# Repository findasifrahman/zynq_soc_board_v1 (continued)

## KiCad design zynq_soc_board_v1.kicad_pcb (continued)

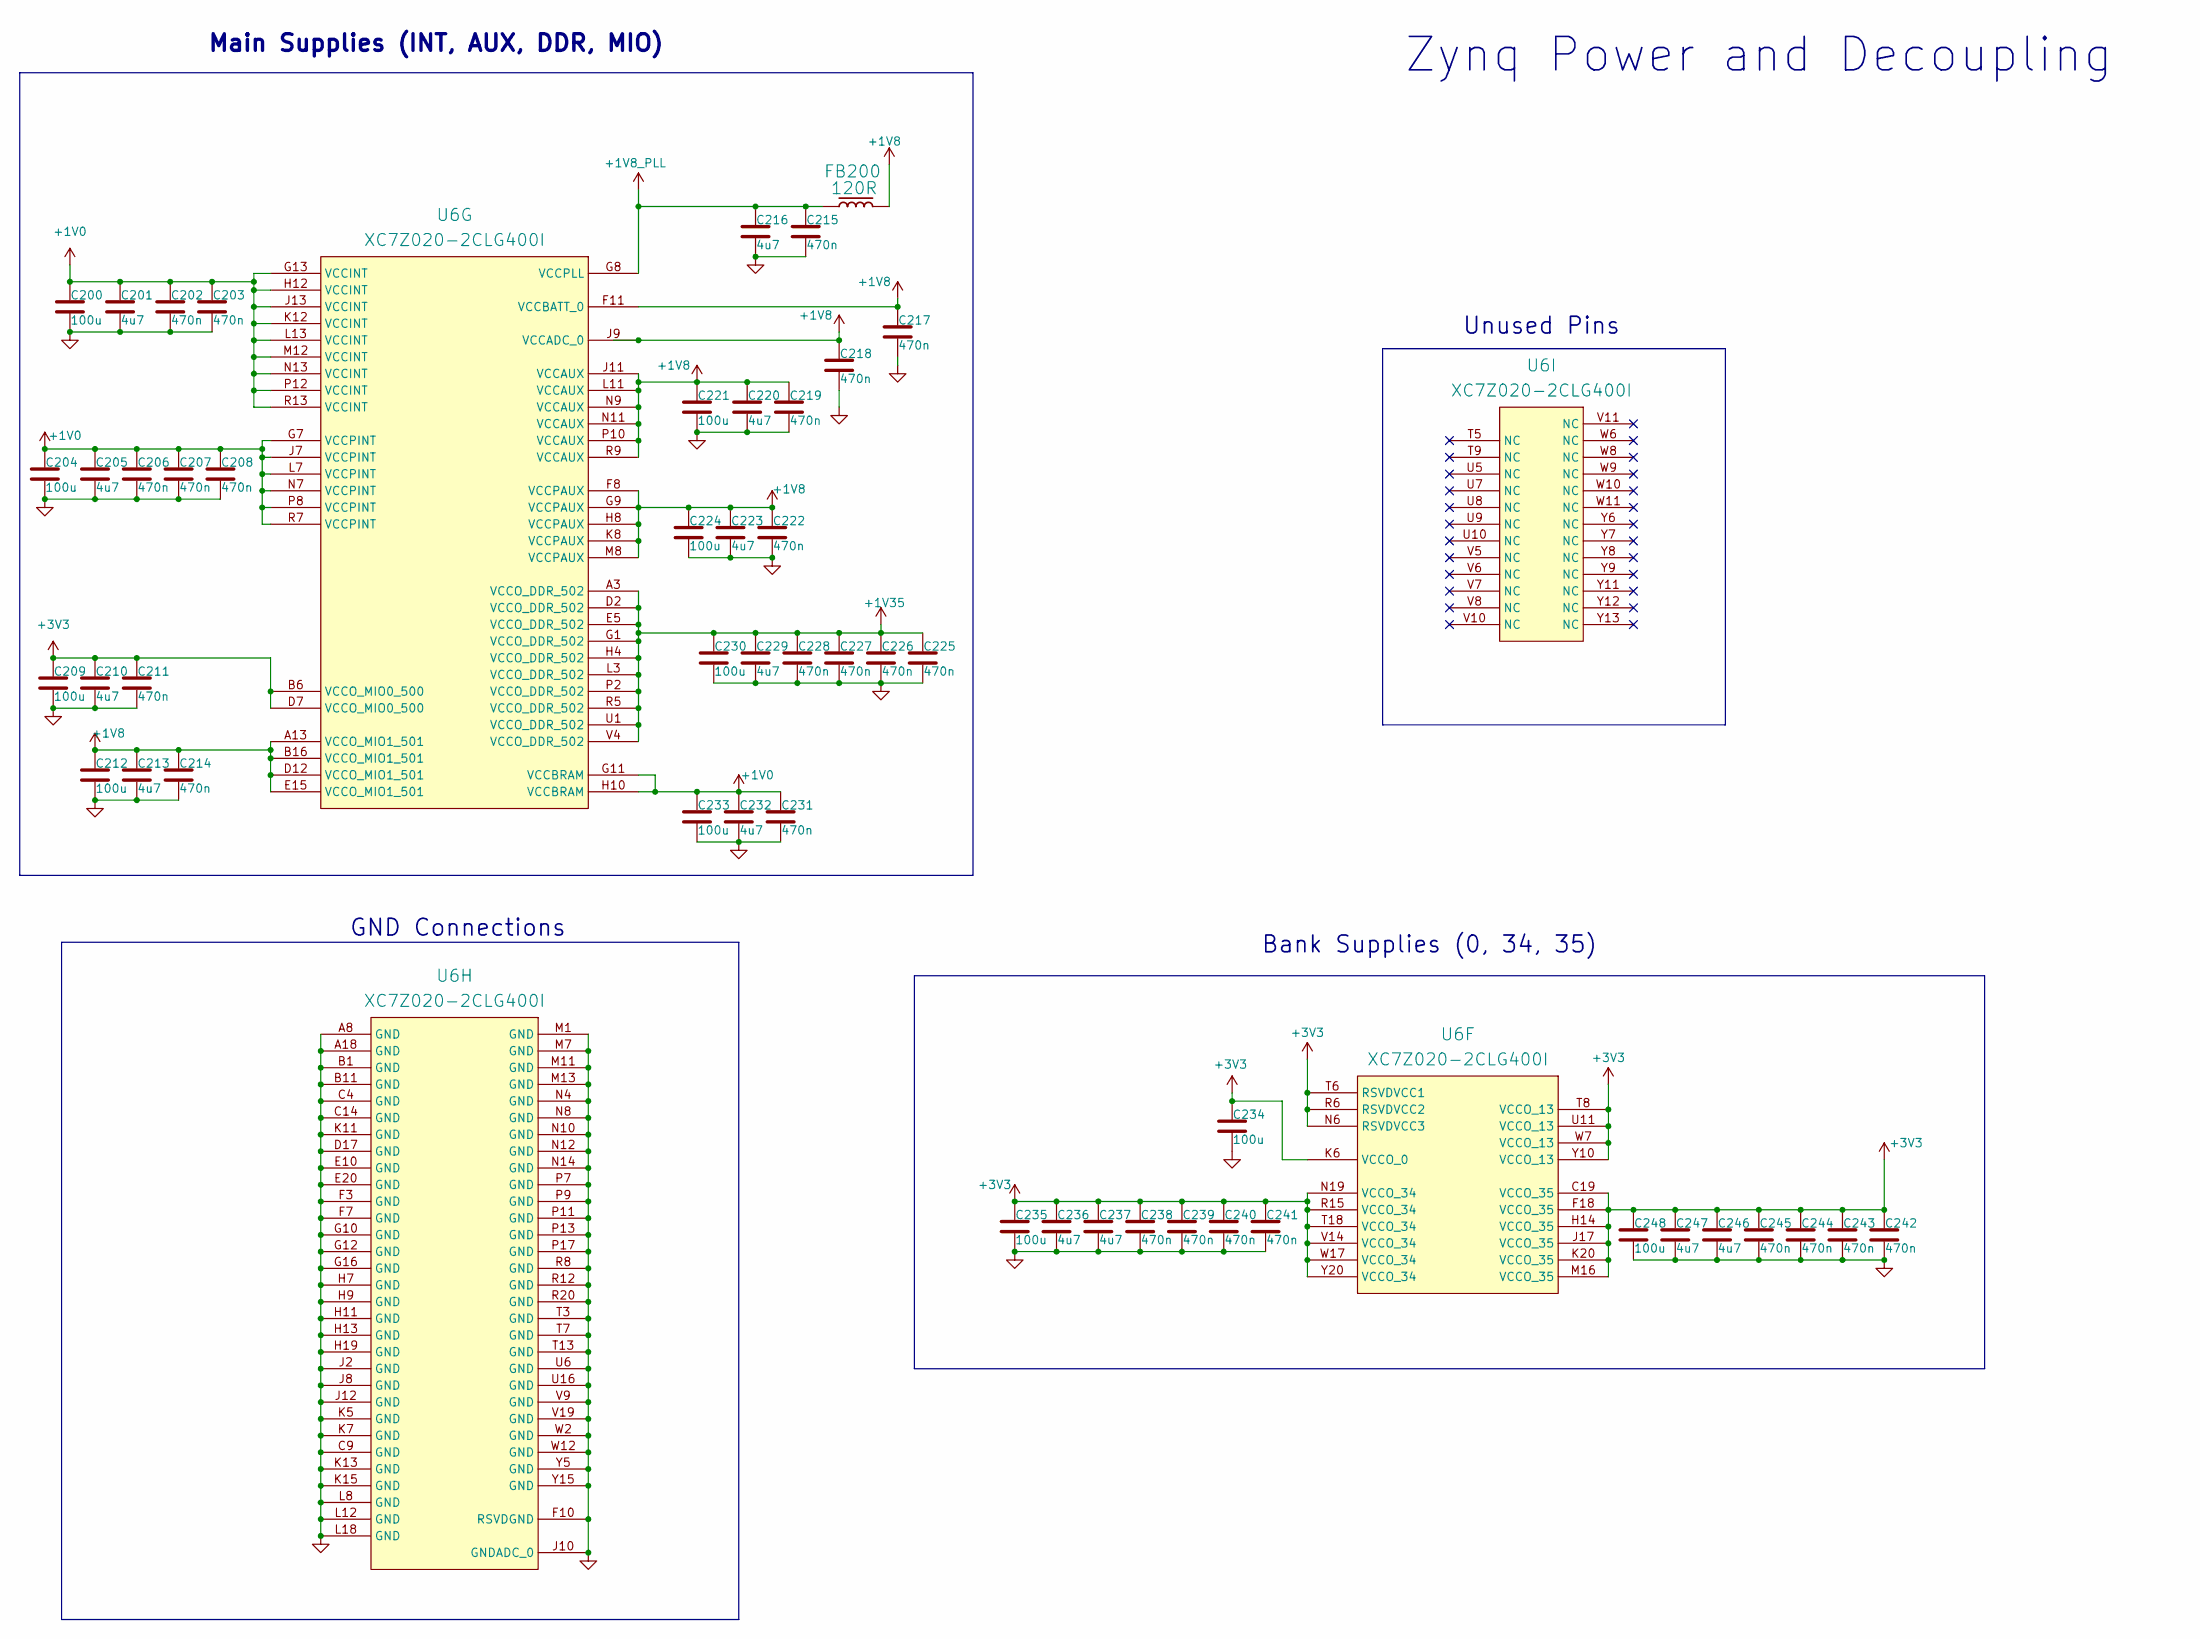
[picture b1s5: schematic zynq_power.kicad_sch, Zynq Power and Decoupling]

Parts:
C200, C204, C209, C212, C221, C224, C230, C233, C234, C235, C248: 100u; C_1206_3216Metric; Manufacturer Part Number CL31A107MQHNNNE; LCSC C15008
C201, C205, C210, C213, C216, C220, C223, C229, C232, C236, C237, C246, C247: 4u7; C_0402_1005Metric; Manufacturer Part Number CL05A475MP5NRNC; LCSC C23733
C202, C203, C206, C207, C208, C211, C214, C215, C217, C218, C219, C222, C225, C226, C227, C228, C231, C238, C239, C240, C241, C242, C243, C244, C245: 470n; C0201; Manufacturer Part Number C0603X5R1A474MT00NE; LCSC C76591
FB200: 120R; FB_0402; Manufacturer Part Number GZ1005D121TF; LCSC C38480
U6: XC7Z020-2CLG400I; Xilinx_CLG400; PartNumber XC7Z010-1CLG400C; LCSC C569043

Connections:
+1V0: C200.1, C201.1, C202.1, C203.1, C204.1, C205.1, C206.1, C207.1, C208.1, C231.1, C232.1, C233.1, U6.G7 (VCCPINT), U6.G11 (VCCBRAM), U6.G13 (VCCINT), U6.H10 (VCCBRAM), U6.H12 (VCCINT), U6.J7 (VCCPINT), U6.J13 (VCCINT), U6.K12 (VCCINT), U6.L7 (VCCPINT), U6.L13 (VCCINT), U6.M12 (VCCINT), U6.N7 (VCCPINT), U6.N13 (VCCINT), U6.P8 (VCCPINT), U6.P12 (VCCINT), U6.R7 (VCCPINT), U6.R13 (VCCINT); also elsewhere on the board
+1V8: C212.1, C213.1, C214.1, C217.1, C218.1, C219.1, C220.1, C221.1, C222.1, C223.1, C224.1, FB200.2, U6.A13 (VCCO_MIO1_501), U6.B16 (VCCO_MIO1_501), U6.D12 (VCCO_MIO1_501), U6.E15 (VCCO_MIO1_501), U6.F8 (VCCPAUX), U6.F11 (VCCBATT_0), U6.G9 (VCCPAUX), U6.H8 (VCCPAUX), U6.J9 (VCCADC_0), U6.J11 (VCCAUX), U6.K8 (VCCPAUX), U6.L11 (VCCAUX), U6.M8 (VCCPAUX), U6.N9 (VCCAUX), U6.N11 (VCCAUX), U6.P10 (VCCAUX), U6.R9 (VCCAUX); also elsewhere on the board
+1V8_PLL: C215.1, C216.1, FB200.1, U6.G8 (VCCPLL)
+1V35: C225.1, C226.1, C227.1, C228.1, C229.1, C230.1, U6.A3 (VCCO_DDR_502), U6.D2 (VCCO_DDR_502), U6.E5 (VCCO_DDR_502), U6.G1 (VCCO_DDR_502), U6.H4 (VCCO_DDR_502), U6.L3 (VCCO_DDR_502), U6.P2 (VCCO_DDR_502), U6.R5 (VCCO_DDR_502), U6.U1 (VCCO_DDR_502), U6.V4 (VCCO_DDR_502); also elsewhere on the board
+3V3: C209.1, C210.1, C211.1, C234.1, C235.1, C236.1, C237.1, C238.1, C239.1, C240.1, C241.1, C242.1, C243.1, C244.1, C245.1, C246.1, C247.1, C248.1, U6.B6 (VCCO_MIO0_500), U6.C19 (VCCO_35), U6.D7 (VCCO_MIO0_500), U6.F18 (VCCO_35), U6.H14 (VCCO_35), U6.J17 (VCCO_35), U6.K6 (VCCO_0), U6.K20 (VCCO_35), U6.M16 (VCCO_35), U6.N6 (RSVDVCC3), U6.N19 (VCCO_34), U6.R6 (RSVDVCC2), U6.R15 (VCCO_34), U6.T6 (RSVDVCC1), U6.T8 (VCCO_13), U6.T18 (VCCO_34), U6.U11 (VCCO_13), U6.V14 (VCCO_34), U6.W7 (VCCO_13), U6.W17 (VCCO_34), U6.Y10 (VCCO_13), U6.Y20 (VCCO_34); also elsewhere on the board
GND: C200.2, C201.2, C202.2, C203.2, C204.2, C205.2, C206.2, C207.2, C208.2, C209.2, C210.2, C211.2, C212.2, C213.2, C214.2, C215.2, C216.2, C217.2, C218.2, C219.2, C220.2, C221.2, C222.2, C223.2, C224.2, C225.2, C226.2, C227.2, C228.2, C229.2, C230.2, C231.2, C232.2, C233.2, C234.2, C235.2, C236.2, C237.2, C238.2, C239.2, C240.2, C241.2, C242.2, C243.2, C244.2, C245.2, C246.2, C247.2, C248.2, U6.A8 (GND), U6.A18 (GND), U6.B1 (GND), U6.B11 (GND), U6.C4 (GND), U6.C9 (GND), U6.C14 (GND), U6.D17 (GND), U6.E10 (GND), U6.E20 (GND), U6.F3 (GND), U6.F7 (GND), U6.F10 (RSVDGND), U6.G10 (GND), U6.G12 (GND), U6.G16 (GND), U6.H7 (GND), U6.H9 (GND), U6.H11 (GND), U6.H13 (GND), U6.H19 (GND), U6.J2 (GND), U6.J8 (GND), U6.J10 (GNDADC_0), U6.J12 (GND), U6.K5 (GND), U6.K7 (GND), U6.K11 (GND), U6.K13 (GND), U6.K15 (GND), U6.L8 (GND), U6.L12 (GND), U6.L18 (GND), U6.M1 (GND), U6.M7 (GND), U6.M11 (GND), U6.M13 (GND), U6.N4 (GND), U6.N8 (GND), U6.N10 (GND), U6.N12 (GND), U6.N14 (GND), U6.P7 (GND), U6.P9 (GND), U6.P11 (GND), U6.P13 (GND), U6.P17 (GND), U6.R8 (GND), U6.R12 (GND), U6.R20 (GND), U6.T3 (GND), U6.T7 (GND), U6.T13 (GND), U6.U6 (GND), U6.U16 (GND), U6.V9 (GND), U6.V19 (GND), U6.W2 (GND), U6.W12 (GND), U6.Y5 (GND), U6.Y15 (GND); also elsewhere on the board

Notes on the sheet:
Main Supplies (INT, AUX, DDR, MIO)
GND Connections
Unused Pins
Zynq Power and Decoupling
Bank Supplies (0, 34, 35)

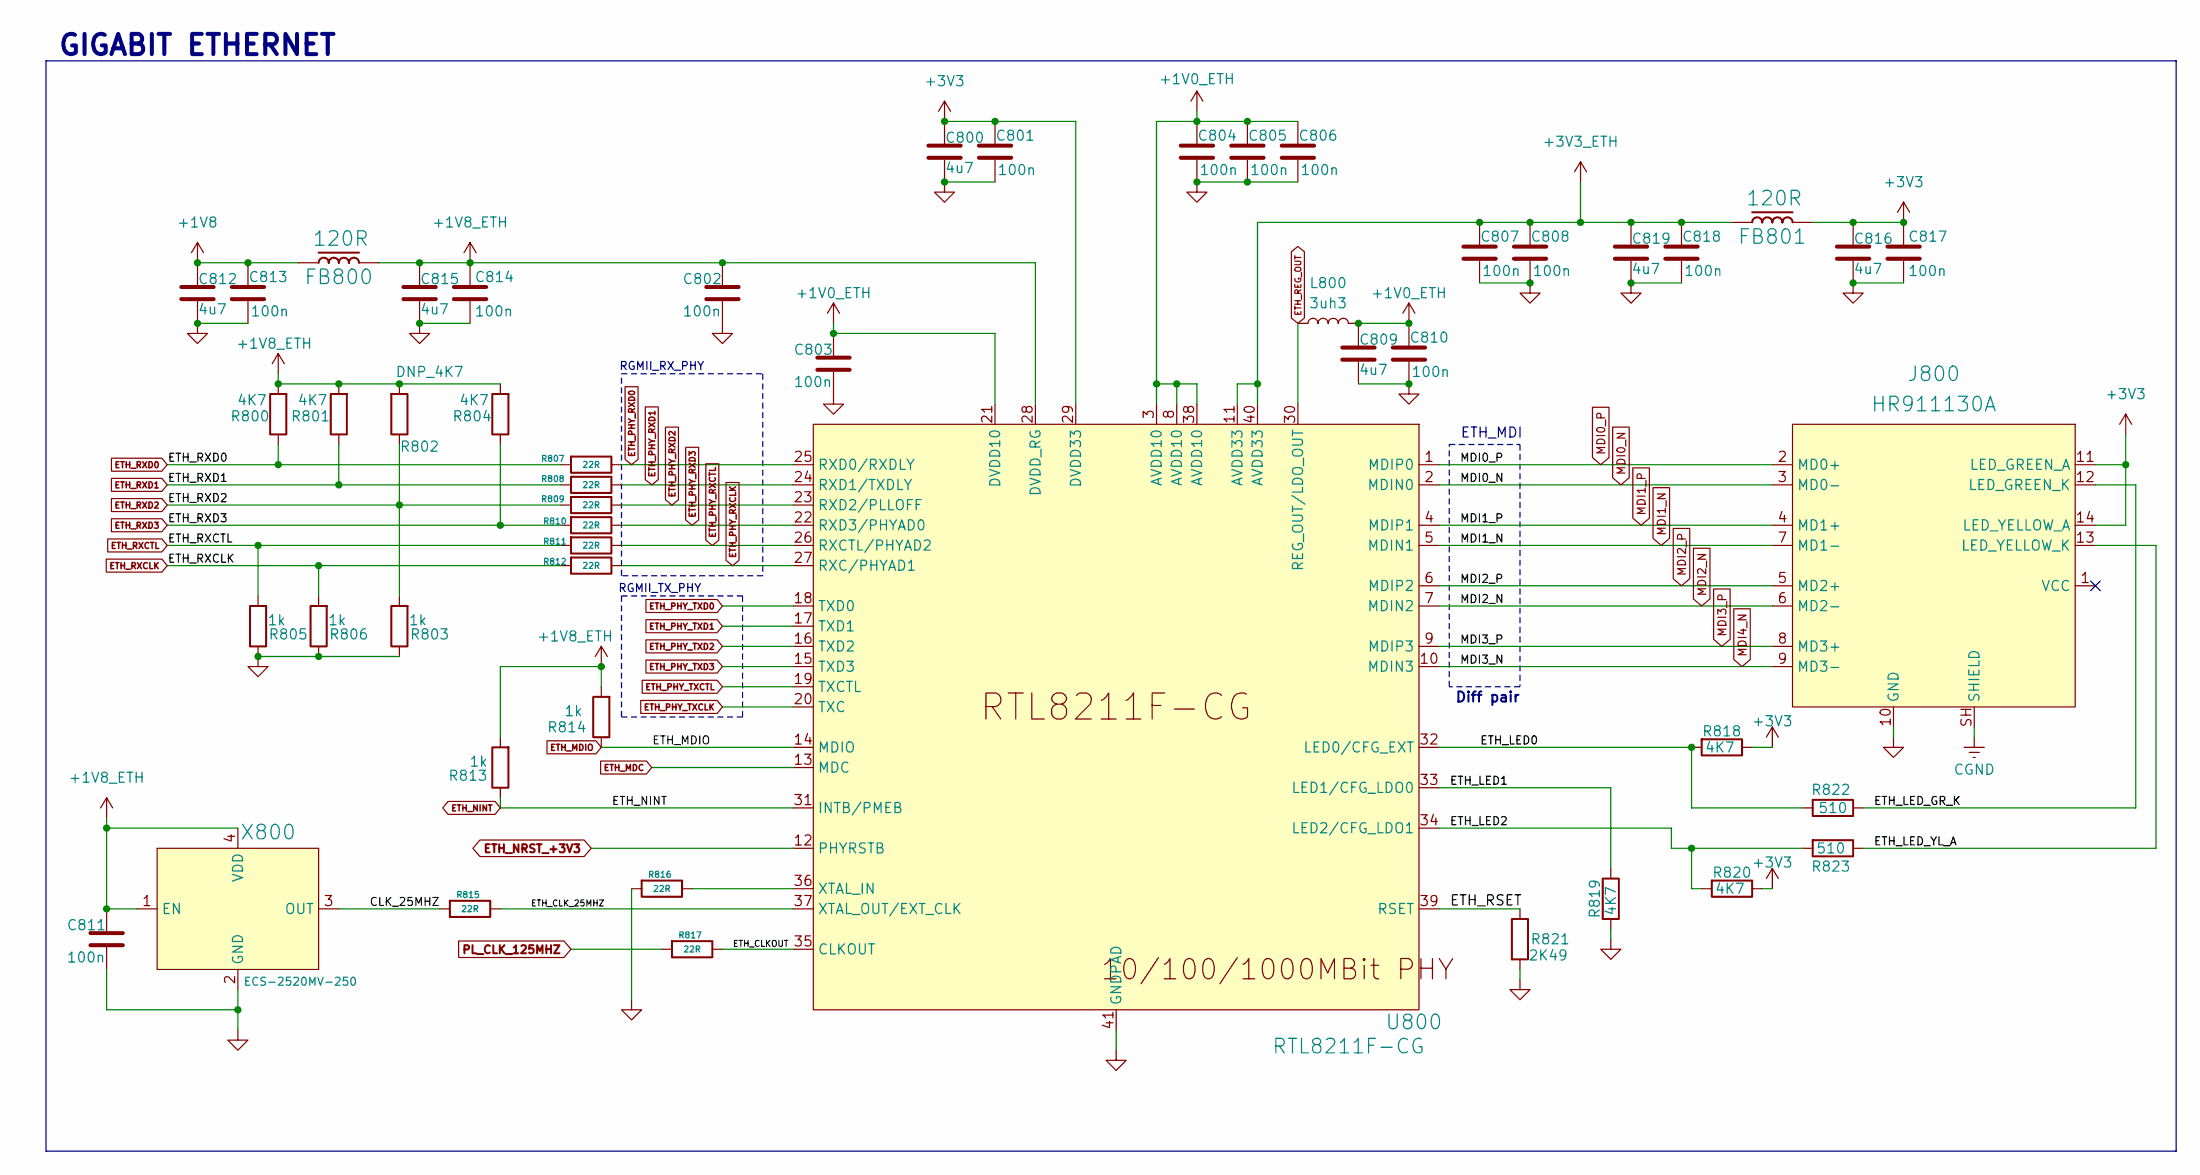
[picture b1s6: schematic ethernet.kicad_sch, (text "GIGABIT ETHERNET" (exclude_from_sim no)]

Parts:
C800, C809, C812, C815, C816, C819: 4u7; C_0402_1005Metric; Manufacturer Part Number CL05A475MP5NRNC; LCSC C23733
C801, C802, C803, C804, C805, C806, C807, C808, C810, C811, C813, C814, C817, C818: 100n; C_0402_1005Metric; Manufacturer Part Number CL05B104KO5NNNC; LCSC C1525
FB800, FB801: 120R; FB_0402; Manufacturer Part Number GZ1005D121TF; LCSC C38480
J800: HR911130A; Manufacturer Part Number HR911130A; LCSC C54408
L800: 3uh3; L_0603_1608Metric; Manufacturer Part Number LQM18PN3R3MFRL; LCSC C162581
R800, R801, R804, R818, R819, R820: 4K7; R_0402_1005Metric; Manufacturer Part Number 0402WGF4701TCE; LCSC C25900
R802: DNP_4K7; R_0402_1005Metric
R803, R805, R806, R813, R814: 1k; R_0402_1005Metric; Manufacturer Part Number 0402WGF1001TCE; LCSC C11702
R807, R808, R809, R810, R811, R812, R815, R816, R817: 22R; R_0402_1005Metric; Manufacturer Part Number 0402WGF220JTCE; LCSC C25092
R821: 2K49; R_0402_1005Metric; Manufacturer Part Number 0402WGF2491TCE; LCSC C25884
R822, R823: 510; R_0402_1005Metric; Manufacturer Part Number RC-02W511JT; LCSC C1119
U800: RTL8211F-CG; WQFN-40_L5.0-W5.0-P0.4-BL-EP; Manufacturer Part Number RTL8211F-CG; LCSC C187932
X800: ECS-2520MV-250; XTAL_2520; Manufacturer Part Number ECS-2520MV-250-BN-TR; LCSC C405463

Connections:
+1V0_ETH: C803.1, C804.1, C805.1, C806.1, C809.1, C810.1, L800.2, U800.3 (AVDD10), U800.8 (AVDD10), U800.21 (DVDD10), U800.38 (AVDD10)
+1V8: C812.1, C813.1, FB800.1; also elsewhere on the board
+1V8_ETH: C802.1, C811.1, C814.1, C815.1, FB800.2, R800.2, R801.2, R802.2, R804.2, R813.2, R814.2, U800.28 (DVDD_RG), X800.1 (EN), X800.4 (VDD)
+3V3: C800.1, C801.1, C816.1, C817.1, FB801.2, J800.11 (LED_GREEN_A), J800.14 (LED_YELLOW_A), R818.1, R820.1, U800.29 (DVDD33); also elsewhere on the board
+3V3_ETH: C807.1, C808.1, C818.1, C819.1, FB801.1, U800.11 (AVDD33), U800.40 (AVDD33)
/ethernet_gigabit/CLK_25MHZ: R815.2, X800.3 (OUT)
/ethernet_gigabit/ETH_CLKOUT: R817.1, U800.35 (CLKOUT)
/ethernet_gigabit/ETH_CLK_25MHZ: R815.1, U800.37 (XTAL_OUT/EXT_CLK)
/ethernet_gigabit/ETH_LED0: R818.2, R822.2, U800.32 (LED0/CFG_EXT)
/ethernet_gigabit/ETH_LED1: R819.1, U800.33 (LED1/CFG_LDO0)
/ethernet_gigabit/ETH_LED2: R820.2, R823.2, U800.34 (LED2/CFG_LDO1)
/ethernet_gigabit/ETH_LED_GR_K: J800.12 (LED_GREEN_K), R822.1
/ethernet_gigabit/ETH_LED_YL_A: J800.13 (LED_YELLOW_K), R823.1
/ethernet_gigabit/ETH_RSET: R821.1, U800.39 (RSET)
CGND: J800.SH (SHIELD); also elsewhere on the board
ETH_MDC: U800.13 (MDC); also elsewhere on the board
ETH_MDIO: R814.1, U800.14 (MDIO); also elsewhere on the board
ETH_NINT: R813.1, U800.31 (INTB/PMEB); also elsewhere on the board
ETH_NRST_+3V3: U800.12 (PHYRSTB); also elsewhere on the board
ETH_PHY_RXCLK: R812.1, U800.27 (RXC/PHYAD1)
ETH_PHY_RXCTL: R811.1, U800.26 (RXCTL/PHYAD2)
ETH_PHY_RXD0: R807.1, U800.25 (RXD0/RXDLY)
ETH_PHY_RXD1: R808.1, U800.24 (RXD1/TXDLY)
ETH_PHY_RXD2: R809.1, U800.23 (RXD2/PLLOFF)
ETH_PHY_RXD3: R810.1, U800.22 (RXD3/PHYAD0)
ETH_PHY_TXCLK: U800.20 (TXC); also elsewhere on the board
ETH_PHY_TXCTL: U800.19 (TXCTL); also elsewhere on the board
ETH_PHY_TXD0: U800.18 (TXD0); also elsewhere on the board
ETH_PHY_TXD1: U800.17 (TXD1); also elsewhere on the board
ETH_PHY_TXD2: U800.16 (TXD2); also elsewhere on the board
ETH_PHY_TXD3: U800.15 (TXD3); also elsewhere on the board
ETH_REG_OUT: L800.1, U800.30 (REG_OUT/LDO_OUT)
ETH_RXCLK: R806.2, R812.2; also elsewhere on the board
ETH_RXCTL: R805.2, R811.2; also elsewhere on the board
ETH_RXD0: R800.1, R807.2; also elsewhere on the board
ETH_RXD1: R801.1, R808.2; also elsewhere on the board
ETH_RXD2: R802.1, R803.2, R809.2; also elsewhere on the board
ETH_RXD3: R804.1, R810.2; also elsewhere on the board
GND: C800.2, C801.2, C802.2, C803.2, C804.2, C805.2, C806.2, C807.2, C808.2, C809.2, C810.2, C811.2, C812.2, C813.2, C814.2, C815.2, C816.2, C817.2, C818.2, C819.2, J800.10 (GND), R803.1, R805.1, R806.1, R816.2, R819.2, R821.2, U800.41 (GNDPAD), X800.2 (GND); also elsewhere on the board
MDI0_N: J800.3 (MD0-), U800.2 (MDIN0)
MDI0_P: J800.2 (MD0+), U800.1 (MDIP0)
MDI1_N: J800.7 (MD1-), U800.5 (MDIN1)
MDI1_P: J800.4 (MD1+), U800.4 (MDIP1)
MDI2_N: J800.6 (MD2-), U800.7 (MDIN2)
MDI2_P: J800.5 (MD2+), U800.6 (MDIP2)
MDI3_P: J800.8 (MD3+), U800.9 (MDIP3)
MDI4_N: J800.9 (MD3-), U800.10 (MDIN3)
unnamed: R816.1, U800.36 (XTAL_IN)
PL_CLK_125MHZ: R817.2; also elsewhere on the board

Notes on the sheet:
ETH_MDI
Diff pair
RGMII_TX_PHY
GIGABIT ETHERNET
RGMII_RX_PHY

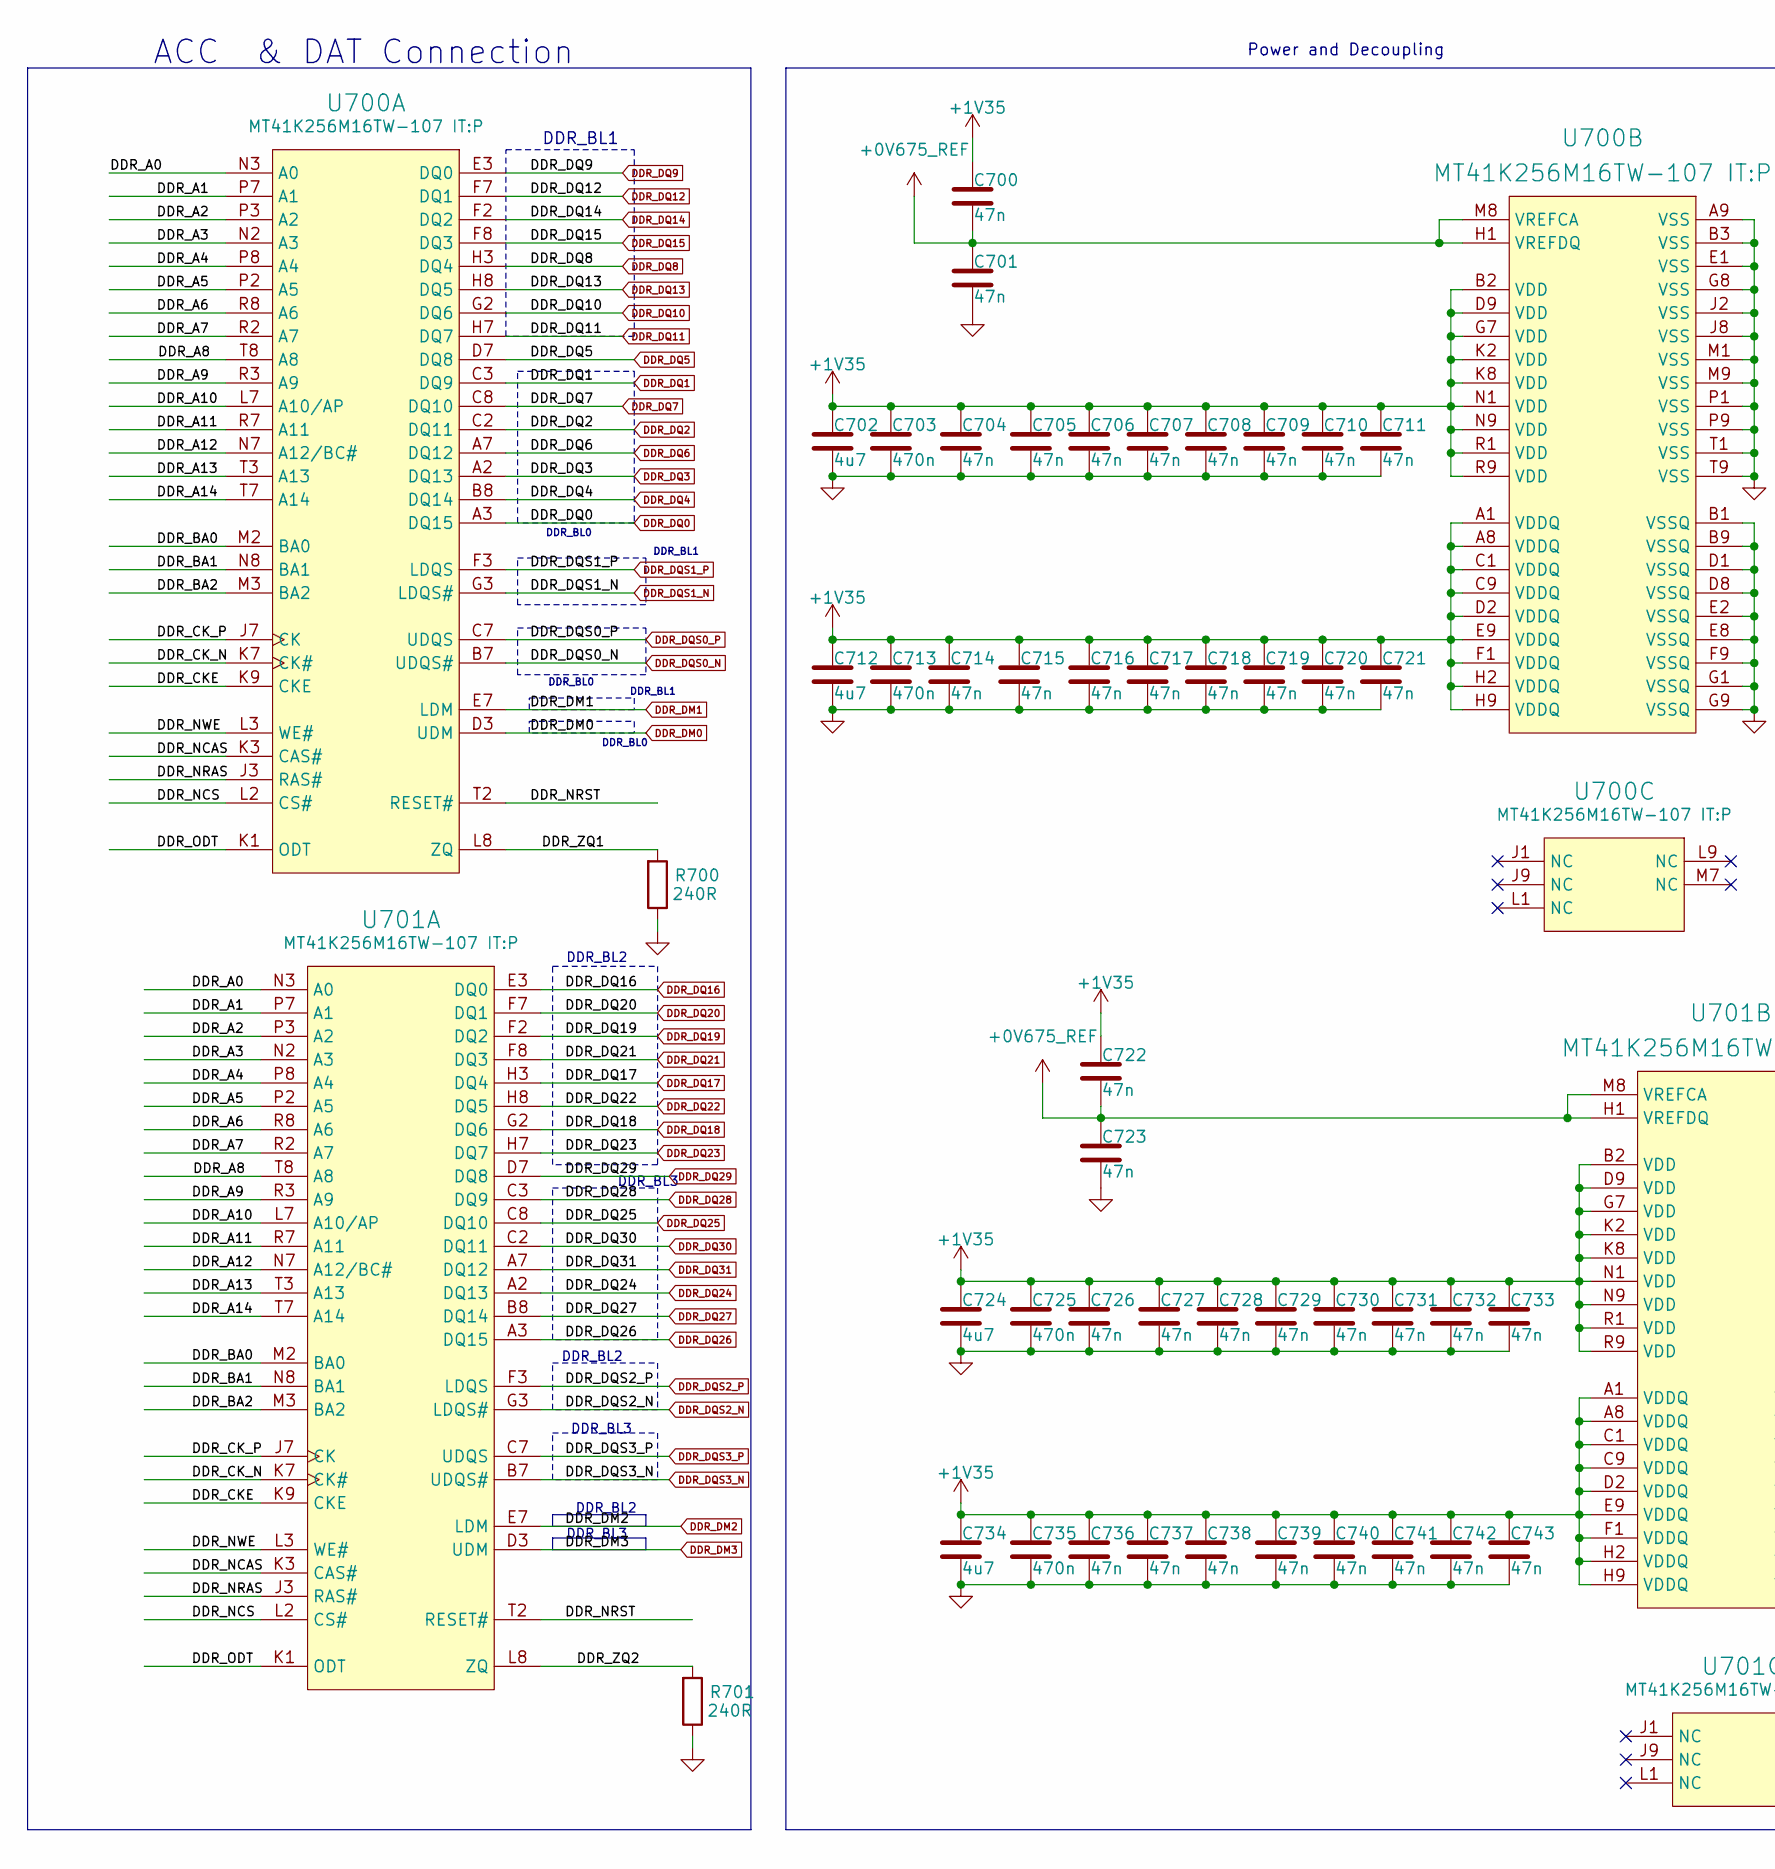
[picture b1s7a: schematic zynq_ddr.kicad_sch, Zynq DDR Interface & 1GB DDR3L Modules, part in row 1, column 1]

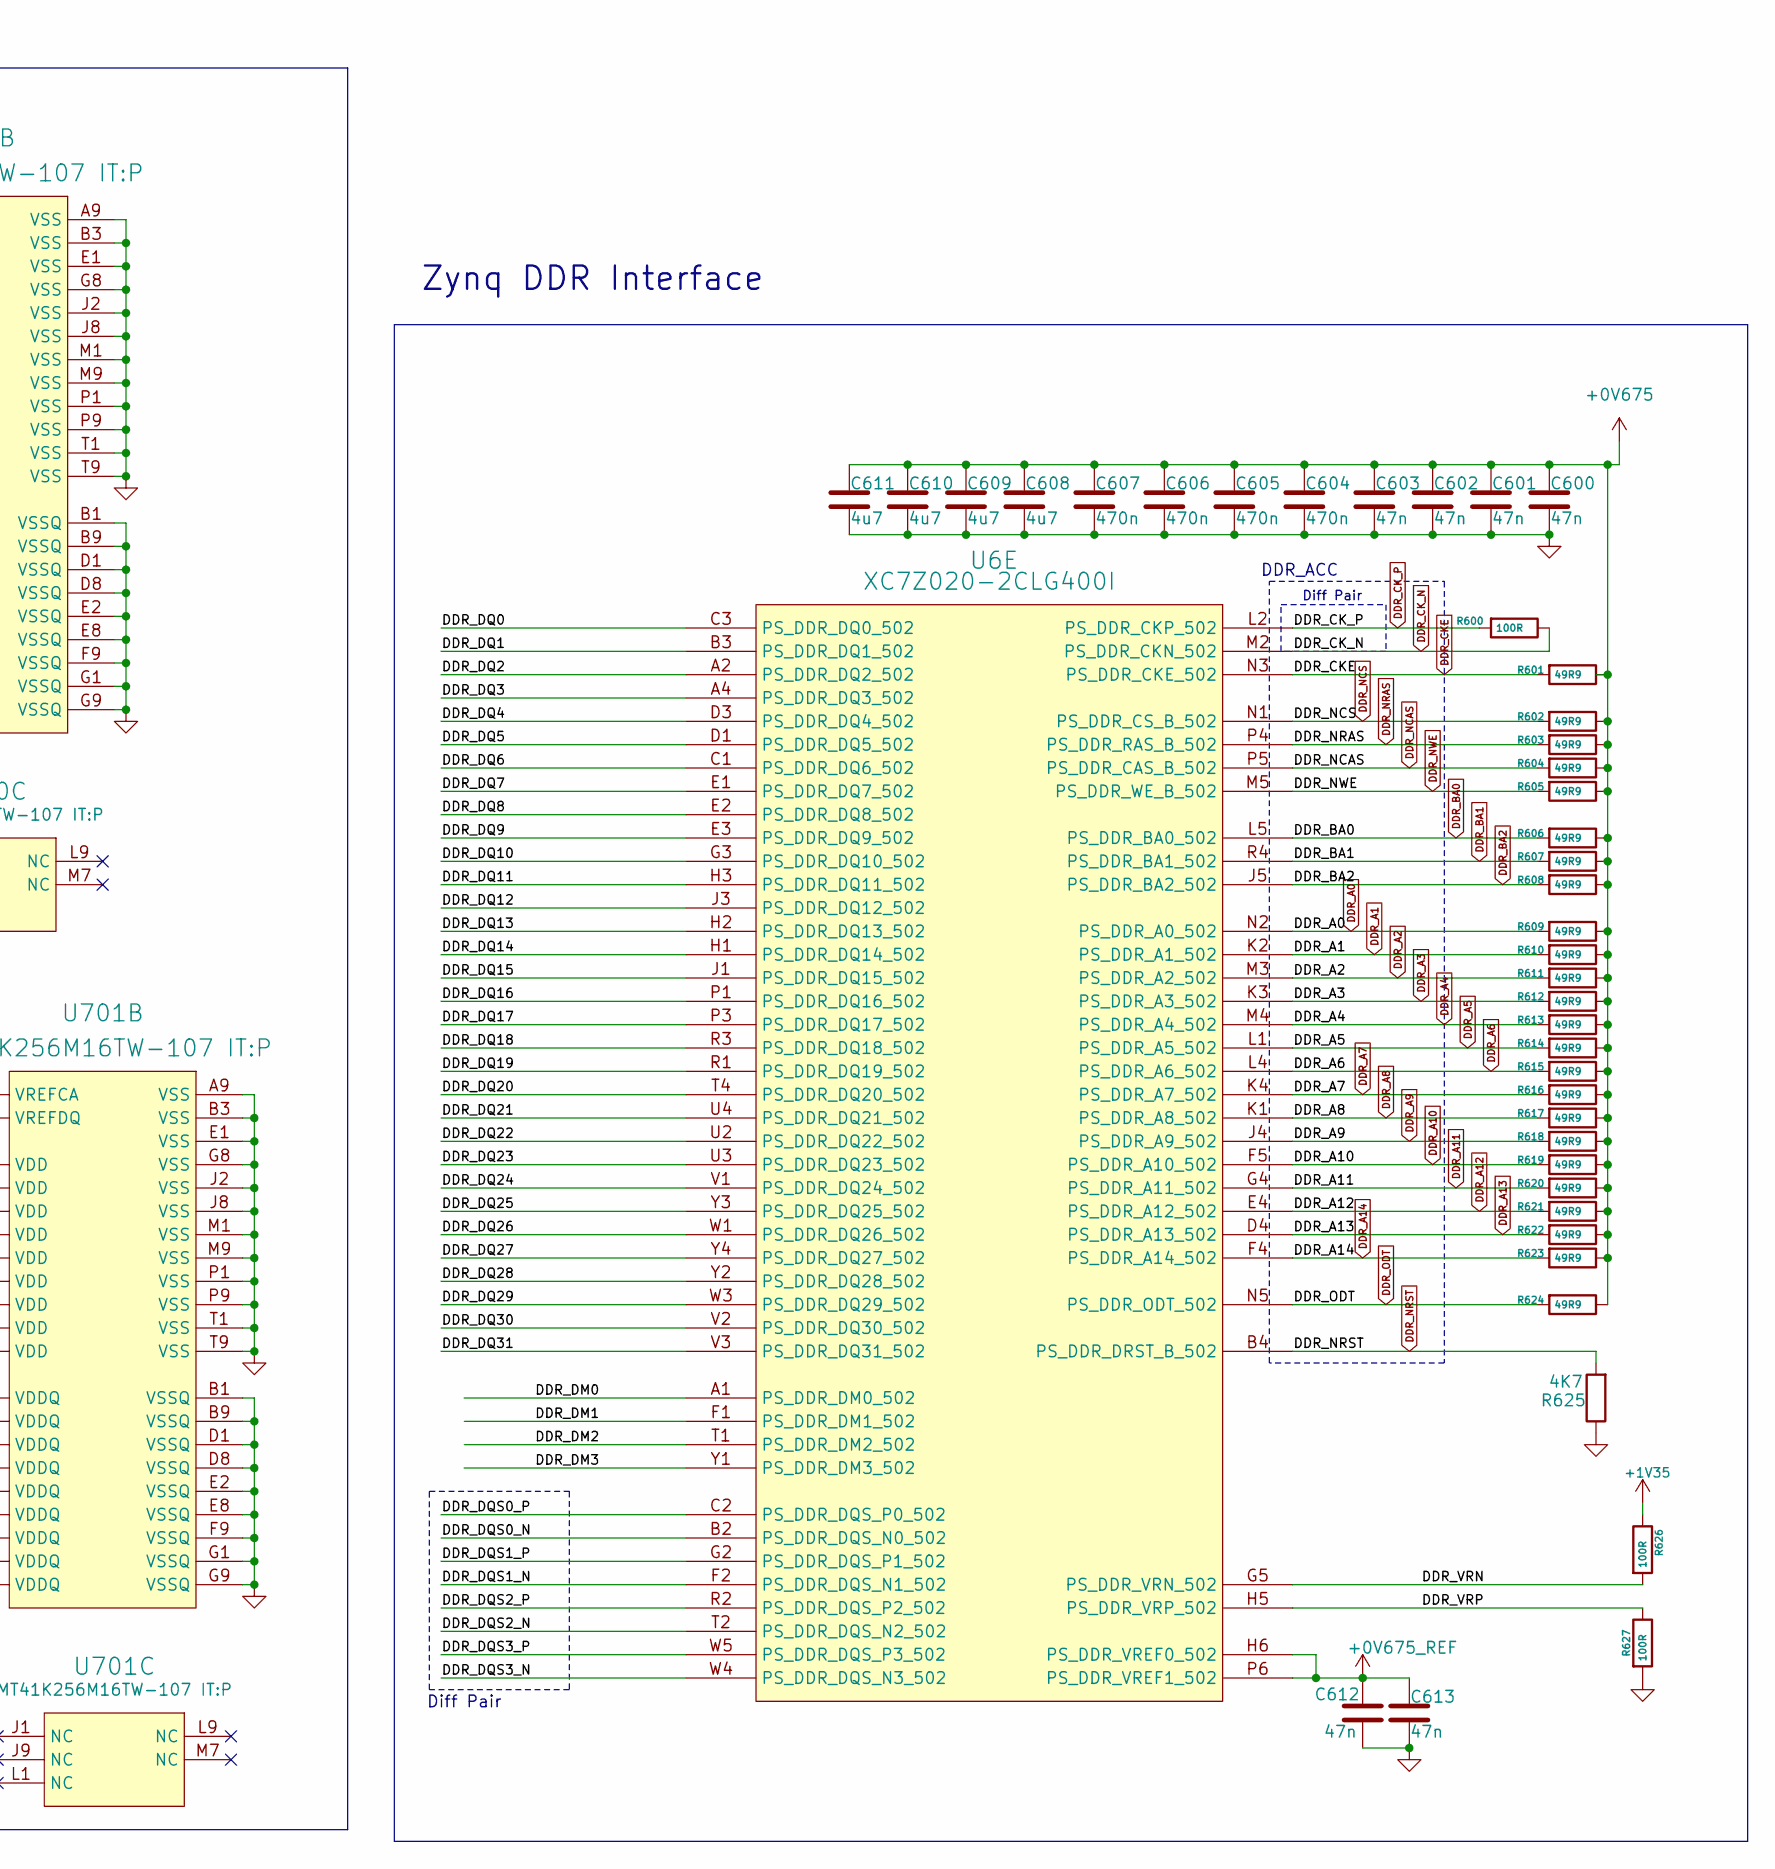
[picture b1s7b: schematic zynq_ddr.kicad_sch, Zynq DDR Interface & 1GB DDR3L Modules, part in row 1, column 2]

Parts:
C600, C601, C602, C603, C612, C613, C700, C701, C704, C705, C706, C707, C708, C709, C710, C711, C714, C715, C716, C717, C718, C719, C720, C721, C722, C723: 47n; C0201; Manufacturer Part Number GRM033R61C473KE84D; LCSC C88917
C604, C605, C606, C607, C703, C713: 470n; C0201; Manufacturer Part Number C0603X5R1A474MT00NE; LCSC C76591
C608, C609, C610, C611, C702, C724, C734: 4u7; C_0402_1005Metric; Manufacturer Part Number CL05A475MP5NRNC; LCSC C23733
C712: 4u7; C0201; Manufacturer Part Number CL05A475MP5NRNC; LCSC C23733
C725, C735: 470n; C_0201_0603Metric; Manufacturer Part Number C0603X5R1A474MT00NE; LCSC C76591
C726, C727, C728, C729, C730, C731, C732, C733, C736, C737, C738, C739, C740, C741, C742, C743: 47n; C_0201_0603Metric; Manufacturer Part Number GRM033R61C473KE84D; LCSC C88917
R600, R626, R627: 100R; R0201; Manufacturer Part Number RC0201FR-07100RL; LCSC C77623
R601, R602, R603, R604, R605, R606, R607, R608, R609, R610, R611, R612, R613, R614, R615, R616, R617, R618, R619, R620, R621, R622, R623, R624: 49R9; R0201; Manufacturer Part Number RC0201FR-0749R9L; LCSC C155744
R625: 4K7; R_0402_1005Metric; Manufacturer Part Number 0402WGF4701TCE; LCSC C25900
R700, R701: 240R; R_0402_1005Metric; Manufacturer Part Number 0402WGF2400TCE; LCSC C25094
U6: XC7Z020-2CLG400I; Xilinx_CLG400; PartNumber XC7Z010-1CLG400C; LCSC C569043
U700, U701: MT41K256M16TW-107 IT:P; FBGA-96_L14.0-W8.0-R16-C6-P0.80-TL; Manufacturer Part Number MT41K256M16TW-107 IT:P; LCSC C367428

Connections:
+0V675: C600.1, C601.1, C602.1, C603.1, C604.1, C605.1, C606.1, C607.1, C608.1, C609.1, C610.1, C611.1, R601.1, R602.1, R603.1, R604.1, R605.1, R606.1, R607.1, R608.1, R609.1, R610.1, R611.1, R612.1, R613.1, R614.1, R615.1, R616.1, R617.1, R618.1, R619.1, R620.1, R621.1, R622.1, R623.1, R624.1; also elsewhere on the board
+0V675_REF: C612.1, C613.1, C700.2, C701.1, C722.2, C723.1, U6.H6 (PS_DDR_VREF0_502), U6.P6 (PS_DDR_VREF1_502), U700.H1 (VREFDQ), U700.M8 (VREFCA), U701.H1 (VREFDQ), U701.M8 (VREFCA); also elsewhere on the board
+1V35: C700.1, C702.1, C703.1, C704.1, C705.1, C706.1, C707.1, C708.1, C709.1, C710.1, C711.1, C712.1, C713.1, C714.1, C715.1, C716.1, C717.1, C718.1, C719.1, C720.1, C721.1, C722.1, C724.1, C725.1, C726.1, C727.1, C728.1, C729.1, C730.1, C731.1, C732.1, C733.1, C734.1, C735.1, C736.1, C737.1, C738.1, C739.1, C740.1, C741.1, C742.1, C743.1, R626.1, U700.A1 (VDDQ), U700.A8 (VDDQ), U700.B2 (VDD), U700.C1 (VDDQ), U700.C9 (VDDQ), U700.D2 (VDDQ), U700.D9 (VDD), U700.E9 (VDDQ), U700.F1 (VDDQ), U700.G7 (VDD), U700.H2 (VDDQ), U700.H9 (VDDQ), U700.K2 (VDD), U700.K8 (VDD), U700.N1 (VDD), U700.N9 (VDD), U700.R1 (VDD), U700.R9 (VDD), U701.A1 (VDDQ), U701.A8 (VDDQ), U701.B2 (VDD), U701.C1 (VDDQ), U701.C9 (VDDQ), U701.D2 (VDDQ), U701.D9 (VDD), U701.E9 (VDDQ), U701.F1 (VDDQ), U701.G7 (VDD), U701.H2 (VDDQ), U701.H9 (VDDQ), U701.K2 (VDD), U701.K8 (VDD), U701.N1 (VDD), U701.N9 (VDD), U701.R1 (VDD), U701.R9 (VDD); also elsewhere on the board
/zynq_ddr/DDR_VRN: R626.2, U6.G5 (PS_DDR_VRN_502)
/zynq_ddr/DDR_VRP: R627.1, U6.H5 (PS_DDR_VRP_502)
/zynq_ddr/DDR_ZQ1: R700.2, U700.L8 (ZQ)
/zynq_ddr/DDR_ZQ2: R701.2, U701.L8 (ZQ)
DDR_A0: R609.2, U6.N2 (PS_DDR_A0_502), U700.N3 (A0), U701.N3 (A0)
DDR_A1: R610.2, U6.K2 (PS_DDR_A1_502), U700.P7 (A1), U701.P7 (A1)
DDR_A2: R611.2, U6.M3 (PS_DDR_A2_502), U700.P3 (A2), U701.P3 (A2)
DDR_A3: R612.2, U6.K3 (PS_DDR_A3_502), U700.N2 (A3), U701.N2 (A3)
DDR_A4: R613.2, U6.M4 (PS_DDR_A4_502), U700.P8 (A4), U701.P8 (A4)
DDR_A5: R614.2, U6.L1 (PS_DDR_A5_502), U700.P2 (A5), U701.P2 (A5)
DDR_A6: R615.2, U6.L4 (PS_DDR_A6_502), U700.R8 (A6), U701.R8 (A6)
DDR_A7: R616.2, U6.K4 (PS_DDR_A7_502), U700.R2 (A7), U701.R2 (A7)
DDR_A8: R617.2, U6.K1 (PS_DDR_A8_502), U700.T8 (A8), U701.T8 (A8)
DDR_A9: R618.2, U6.J4 (PS_DDR_A9_502), U700.R3 (A9), U701.R3 (A9)
DDR_A10: R619.2, U6.F5 (PS_DDR_A10_502), U700.L7 (A10/AP), U701.L7 (A10/AP)
DDR_A11: R620.2, U6.G4 (PS_DDR_A11_502), U700.R7 (A11), U701.R7 (A11)
DDR_A12: R621.2, U6.E4 (PS_DDR_A12_502), U700.N7 (A12/BC#), U701.N7 (A12/BC#)
DDR_A13: R622.2, U6.D4 (PS_DDR_A13_502), U700.T3 (A13), U701.T3 (A13)
DDR_A14: R623.2, U6.F4 (PS_DDR_A14_502), U700.T7 (A14), U701.T7 (A14)
DDR_BA0: R606.2, U6.L5 (PS_DDR_BA0_502), U700.M2 (BA0), U701.M2 (BA0)
DDR_BA1: R607.2, U6.R4 (PS_DDR_BA1_502), U700.N8 (BA1), U701.N8 (BA1)
DDR_BA2: R608.2, U6.J5 (PS_DDR_BA2_502), U700.M3 (BA2), U701.M3 (BA2)
DDR_CKE: R601.2, U6.N3 (PS_DDR_CKE_502), U700.K9 (CKE), U701.K9 (CKE)
DDR_CK_N: R600.1, U6.M2 (PS_DDR_CKN_502), U700.K7 (CK#), U701.K7 (CK#)
DDR_CK_P: R600.2, U6.L2 (PS_DDR_CKP_502), U700.J7 (CK), U701.J7 (CK)
DDR_DM0: U6.A1 (PS_DDR_DM0_502), U700.D3 (UDM)
DDR_DM1: U6.F1 (PS_DDR_DM1_502), U700.E7 (LDM)
DDR_DM2: U6.T1 (PS_DDR_DM2_502), U701.E7 (LDM)
DDR_DM3: U6.Y1 (PS_DDR_DM3_502), U701.D3 (UDM)
DDR_DQ0: U6.C3 (PS_DDR_DQ0_502), U700.A3 (DQ15)
DDR_DQ1: U6.B3 (PS_DDR_DQ1_502), U700.C3 (DQ9)
DDR_DQ2: U6.A2 (PS_DDR_DQ2_502), U700.C2 (DQ11)
DDR_DQ3: U6.A4 (PS_DDR_DQ3_502), U700.A2 (DQ13)
DDR_DQ4: U6.D3 (PS_DDR_DQ4_502), U700.B8 (DQ14)
DDR_DQ5: U6.D1 (PS_DDR_DQ5_502), U700.D7 (DQ8)
DDR_DQ6: U6.C1 (PS_DDR_DQ6_502), U700.A7 (DQ12)
DDR_DQ7: U6.E1 (PS_DDR_DQ7_502), U700.C8 (DQ10)
DDR_DQ8: U6.E2 (PS_DDR_DQ8_502), U700.H3 (DQ4)
DDR_DQ9: U6.E3 (PS_DDR_DQ9_502), U700.E3 (DQ0)
DDR_DQ10: U6.G3 (PS_DDR_DQ10_502), U700.G2 (DQ6)
DDR_DQ11: U6.H3 (PS_DDR_DQ11_502), U700.H7 (DQ7)
DDR_DQ12: U6.J3 (PS_DDR_DQ12_502), U700.F7 (DQ1)
DDR_DQ13: U6.H2 (PS_DDR_DQ13_502), U700.H8 (DQ5)
DDR_DQ14: U6.H1 (PS_DDR_DQ14_502), U700.F2 (DQ2)
DDR_DQ15: U6.J1 (PS_DDR_DQ15_502), U700.F8 (DQ3)
DDR_DQ16: U6.P1 (PS_DDR_DQ16_502), U701.E3 (DQ0)
DDR_DQ17: U6.P3 (PS_DDR_DQ17_502), U701.H3 (DQ4)
DDR_DQ18: U6.R3 (PS_DDR_DQ18_502), U701.G2 (DQ6)
DDR_DQ19: U6.R1 (PS_DDR_DQ19_502), U701.F2 (DQ2)
DDR_DQ20: U6.T4 (PS_DDR_DQ20_502), U701.F7 (DQ1)
DDR_DQ21: U6.U4 (PS_DDR_DQ21_502), U701.F8 (DQ3)
DDR_DQ22: U6.U2 (PS_DDR_DQ22_502), U701.H8 (DQ5)
DDR_DQ23: U6.U3 (PS_DDR_DQ23_502), U701.H7 (DQ7)
DDR_DQ24: U6.V1 (PS_DDR_DQ24_502), U701.A2 (DQ13)
DDR_DQ25: U6.Y3 (PS_DDR_DQ25_502), U701.C8 (DQ10)
DDR_DQ26: U6.W1 (PS_DDR_DQ26_502), U701.A3 (DQ15)
DDR_DQ27: U6.Y4 (PS_DDR_DQ27_502), U701.B8 (DQ14)
DDR_DQ28: U6.Y2 (PS_DDR_DQ28_502), U701.C3 (DQ9)
DDR_DQ29: U6.W3 (PS_DDR_DQ29_502), U701.D7 (DQ8)
DDR_DQ30: U6.V2 (PS_DDR_DQ30_502), U701.C2 (DQ11)
DDR_DQ31: U6.V3 (PS_DDR_DQ31_502), U701.A7 (DQ12)
DDR_DQS0_N: U6.B2 (PS_DDR_DQS_N0_502), U700.B7 (UDQS#)
DDR_DQS0_P: U6.C2 (PS_DDR_DQS_P0_502), U700.C7 (UDQS)
DDR_DQS1_N: U6.F2 (PS_DDR_DQS_N1_502), U700.G3 (LDQS#)
DDR_DQS1_P: U6.G2 (PS_DDR_DQS_P1_502), U700.F3 (LDQS)
DDR_DQS2_N: U6.T2 (PS_DDR_DQS_N2_502), U701.G3 (LDQS#)
DDR_DQS2_P: U6.R2 (PS_DDR_DQS_P2_502), U701.F3 (LDQS)
DDR_DQS3_N: U6.W4 (PS_DDR_DQS_N3_502), U701.B7 (UDQS#)
DDR_DQS3_P: U6.W5 (PS_DDR_DQS_P3_502), U701.C7 (UDQS)
DDR_NCAS: R604.2, U6.P5 (PS_DDR_CAS_B_502), U700.K3 (CAS#), U701.K3 (CAS#)
DDR_NCS: R602.2, U6.N1 (PS_DDR_CS_B_502), U700.L2 (CS#), U701.L2 (CS#)
DDR_NRAS: R603.2, U6.P4 (PS_DDR_RAS_B_502), U700.J3 (RAS#), U701.J3 (RAS#)
DDR_NRST: R625.2, U6.B4 (PS_DDR_DRST_B_502), U700.T2 (RESET#), U701.T2 (RESET#)
DDR_NWE: R605.2, U6.M5 (PS_DDR_WE_B_502), U700.L3 (WE#), U701.L3 (WE#)
DDR_ODT: R624.2, U6.N5 (PS_DDR_ODT_502), U700.K1 (ODT), U701.K1 (ODT)
GND: C600.2, C601.2, C602.2, C603.2, C604.2, C605.2, C606.2, C607.2, C608.2, C609.2, C610.2, C611.2, C612.2, C613.2, C701.2, C702.2, C703.2, C704.2, C705.2, C706.2, C707.2, C708.2, C709.2, C710.2, C711.2, C712.2, C713.2, C714.2, C715.2, C716.2, C717.2, C718.2, C719.2, C720.2, C721.2, C723.2, C724.2, C725.2, C726.2, C727.2, C728.2, C729.2, C730.2, C731.2, C732.2, C733.2, C734.2, C735.2, C736.2, C737.2, C738.2, C739.2, C740.2, C741.2, C742.2, C743.2, R625.1, R627.2, R700.1, R701.1, U700.A9 (VSS), U700.B1 (VSSQ), U700.B3 (VSS), U700.B9 (VSSQ), U700.D1 (VSSQ), U700.D8 (VSSQ), U700.E1 (VSS), U700.E2 (VSSQ), U700.E8 (VSSQ), U700.F9 (VSSQ), U700.G1 (VSSQ), U700.G8 (VSS), U700.G9 (VSSQ), U700.J2 (VSS), U700.J8 (VSS), U700.M1 (VSS), U700.M9 (VSS), U700.P1 (VSS), U700.P9 (VSS), U700.T1 (VSS), U700.T9 (VSS), U701.A9 (VSS), U701.B1 (VSSQ), U701.B3 (VSS), U701.B9 (VSSQ), U701.D1 (VSSQ), U701.D8 (VSSQ), U701.E1 (VSS), U701.E2 (VSSQ), U701.E8 (VSSQ), U701.F9 (VSSQ), U701.G1 (VSSQ), U701.G8 (VSS), U701.G9 (VSSQ), U701.J2 (VSS), U701.J8 (VSS), U701.M1 (VSS), U701.M9 (VSS), U701.P1 (VSS), U701.P9 (VSS), U701.T1 (VSS), U701.T9 (VSS); also elsewhere on the board

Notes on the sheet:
ACC & DAT Connection
DDR_BL1
DDR_ACC
DDR_BL3
DDR_BL2
Diff Pair
DDR_BL0
Zynq DDR Interface
Power and Decoupling
